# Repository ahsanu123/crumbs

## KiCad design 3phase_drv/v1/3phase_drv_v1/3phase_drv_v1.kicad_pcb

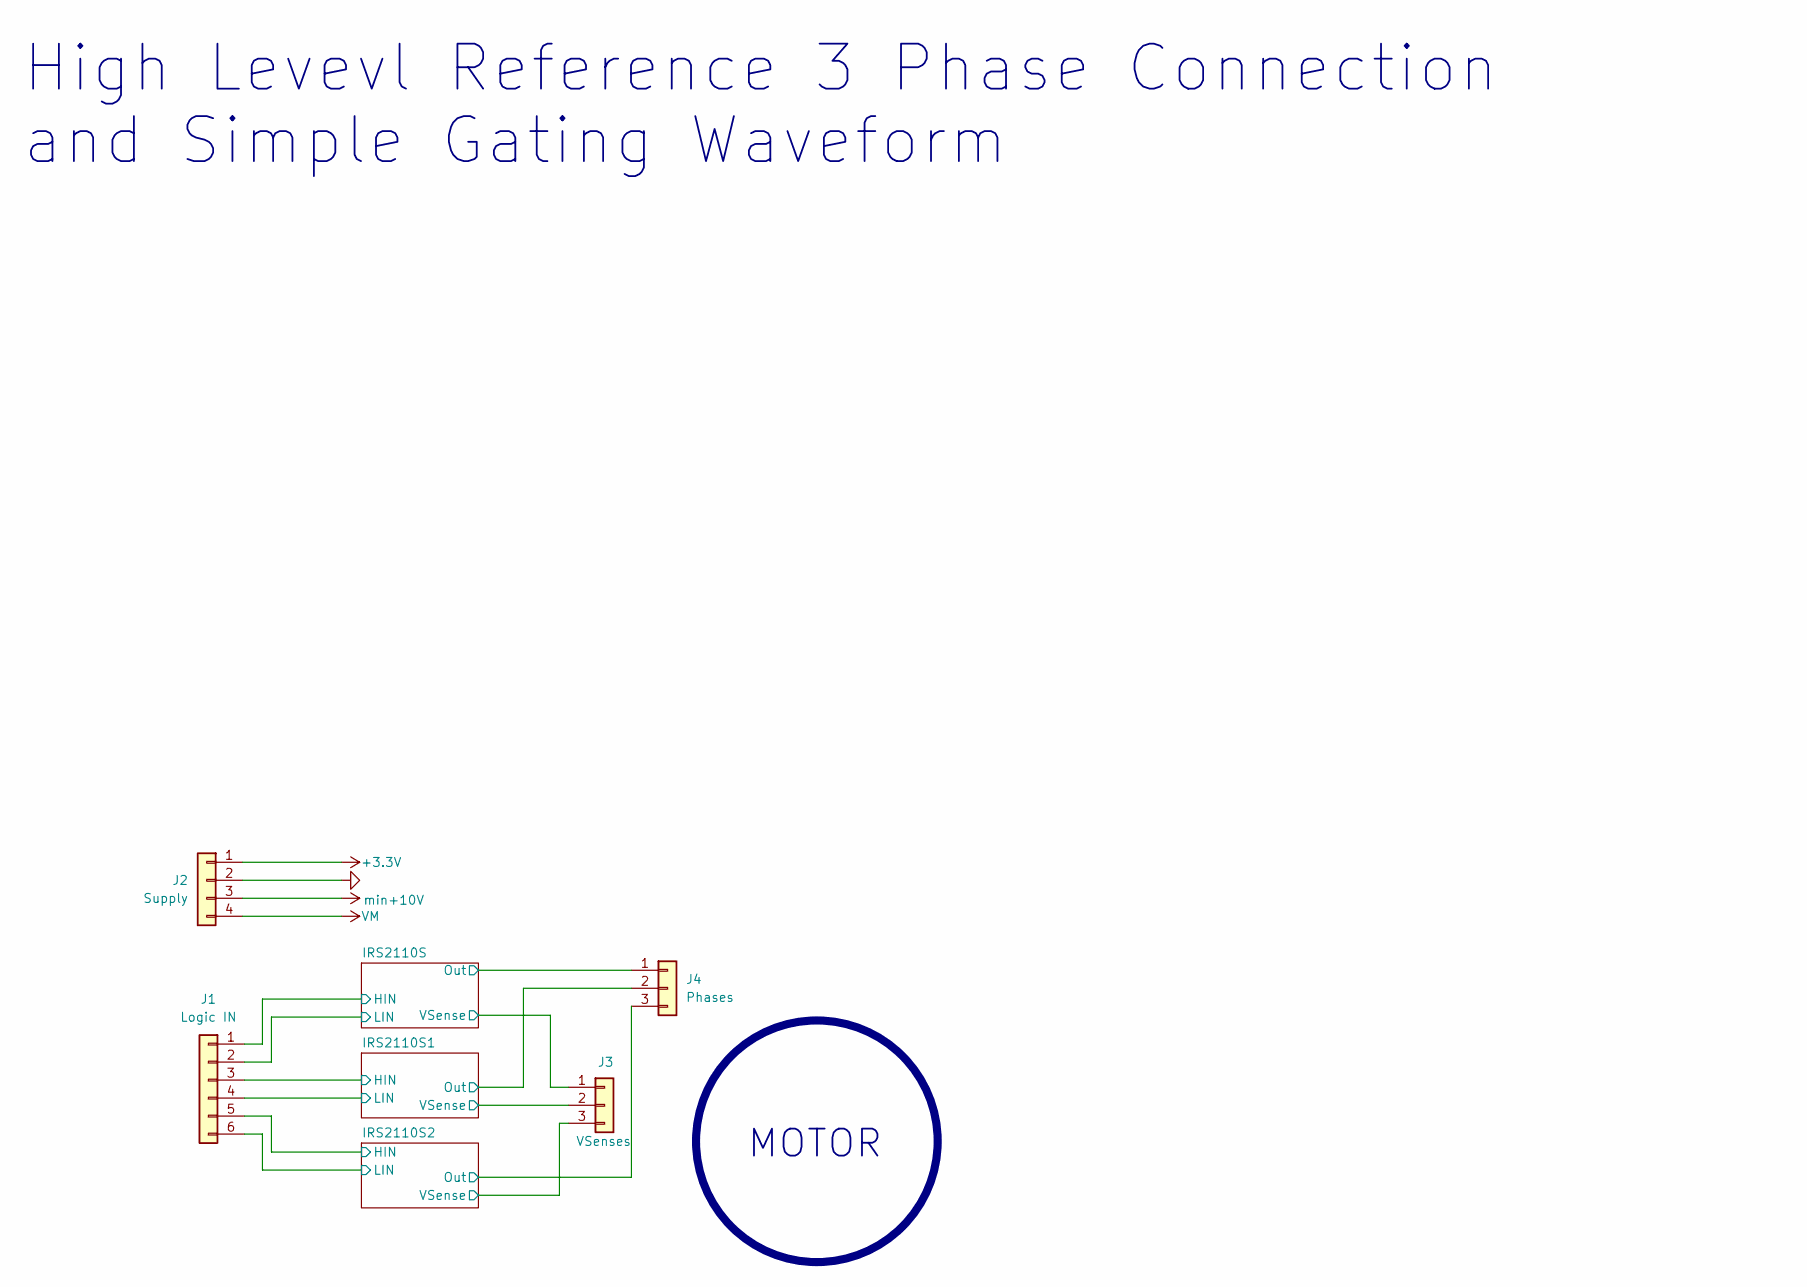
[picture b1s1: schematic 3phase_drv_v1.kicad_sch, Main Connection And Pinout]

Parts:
J1: Logic IN; PinHeader_1x06_P2.54mm_Vertical
J2: Supply; PinHeader_1x04_P2.54mm_Vertical
J3: VSenses; PinHeader_1x03_P2.54mm_Vertical
J4: Phases; PinHeader_1x03_P2.54mm_Vertical

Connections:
+3.3V: J2.1; also elsewhere on the board
/IRS2110S1/HIN: J1.3; also elsewhere on the board
/IRS2110S1/LIN: J1.4; also elsewhere on the board
/IRS2110S1/Out: J4.2; also elsewhere on the board
/IRS2110S1/VSense: J3.2; also elsewhere on the board
/IRS2110S2/HIN: J1.5; also elsewhere on the board
/IRS2110S2/LIN: J1.6; also elsewhere on the board
/IRS2110S2/Out: J4.3; also elsewhere on the board
/IRS2110S2/VSense: J3.3; also elsewhere on the board
/IRS2110S/HIN: J1.1; also elsewhere on the board
/IRS2110S/LIN: J1.2; also elsewhere on the board
/IRS2110S/Out: J4.1; also elsewhere on the board
/IRS2110S/VSense: J3.1; also elsewhere on the board
GND: J2.2; also elsewhere on the board
VM: J2.4; also elsewhere on the board
min+10V: J2.3; also elsewhere on the board

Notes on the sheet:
High Levevl Reference 3 Phase Connection and Simple Gating Waveform
MOTOR

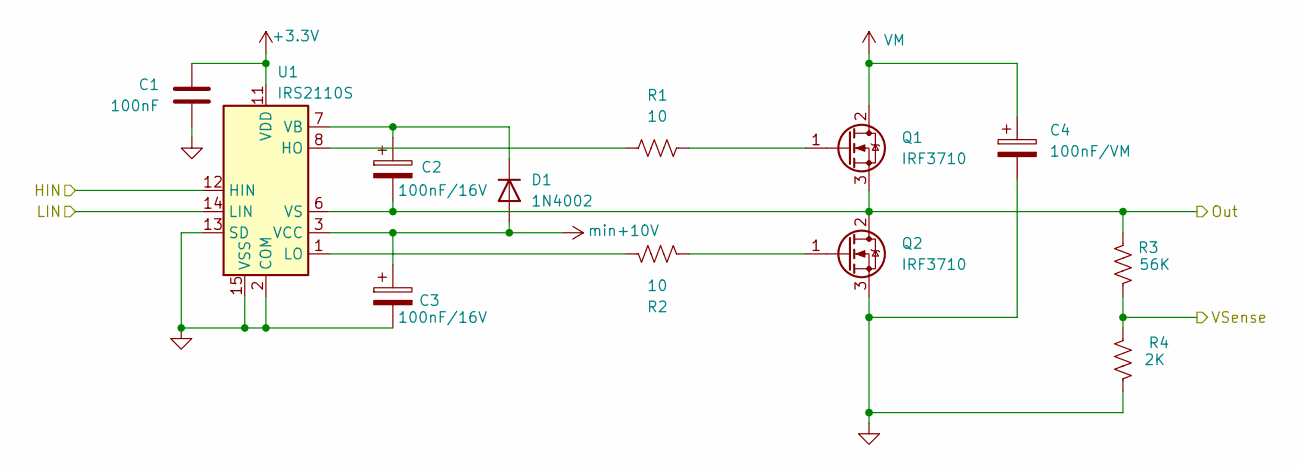
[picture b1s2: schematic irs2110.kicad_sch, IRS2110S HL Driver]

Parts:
C1: 100nF; C_0805_2012Metric
C2, C3: 100nF/16V; CP_Radial_D13.0mm_P5.00mm
C4: 100nF/VM; CP_Radial_D13.0mm_P5.00mm
D1: 1N4002; D_DO-41_SOD81_P10.16mm_Horizontal
Q1, Q2: IRF3710; TO-220-3_Horizontal_TabDown
R1, R2: 10; R_0805_2012Metric
R3: 56K; R_0805_2012Metric
R4: 2K; R_0805_2012Metric
U1: IRS2110S; SOIC-16W_7.5x10.3mm_P1.27mm

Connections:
+3.3V: C1.1, U1.11 (VDD); also elsewhere on the board
/IRS2110S1/HIN: U1.12 (HIN); also elsewhere on the board
/IRS2110S1/LIN: U1.14 (LIN); also elsewhere on the board
/IRS2110S1/Out: C2.2, Q1.3 (S), Q2.2 (D), R3.2, U1.6 (VS); also elsewhere on the board
/IRS2110S1/VSense: R3.1, R4.2; also elsewhere on the board
GND: C1.2, C3.2, C4.2, Q2.3 (S), R4.1, U1.2 (COM), U1.13 (SD), U1.15 (VSS); also elsewhere on the board
unnamed: C2.1, D1.1 (K), U1.7 (VB)
unnamed: Q1.1 (G), R1.2
unnamed: Q2.1 (G), R2.2
unnamed: R1.1, U1.8 (HO)
unnamed: R2.1, U1.1 (LO)
VM: C4.1, Q1.2 (D); also elsewhere on the board
min+10V: C3.1, D1.2 (A), U1.3 (VCC); also elsewhere on the board

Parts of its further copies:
C5, C9: 100nF; C_0805_2012Metric
C6, C7, C10, C11: 100nF/16V; CP_Radial_D13.0mm_P5.00mm
C8, C12: 100nF/VM; CP_Radial_D13.0mm_P5.00mm
D2, D3: 1N4002; D_DO-41_SOD81_P10.16mm_Horizontal
Q3, Q4, Q5, Q6: IRF3710; TO-220-3_Horizontal_TabDown
R5, R6, R9, R10: 10; R_0805_2012Metric
R7, R11: 56K; R_0805_2012Metric
R8, R12: 2K; R_0805_2012Metric
U2, U3: IRS2110S; SOIC-16W_7.5x10.3mm_P1.27mm

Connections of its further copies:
+3.3V: C5.1, C9.1, U2.11 (VDD), U3.11 (VDD); also elsewhere on the board
/IRS2110S2/HIN: U2.12 (HIN); also elsewhere on the board
/IRS2110S2/LIN: U2.14 (LIN); also elsewhere on the board
/IRS2110S2/Out: C6.2, Q3.3 (S), Q4.2 (D), R7.2, U2.6 (VS); also elsewhere on the board
/IRS2110S2/VSense: R7.1, R8.2; also elsewhere on the board
/IRS2110S/HIN: U3.12 (HIN); also elsewhere on the board
/IRS2110S/LIN: U3.14 (LIN); also elsewhere on the board
/IRS2110S/Out: C10.2, Q5.3 (S), Q6.2 (D), R11.2, U3.6 (VS); also elsewhere on the board
/IRS2110S/VSense: R11.1, R12.2; also elsewhere on the board
GND: C5.2, C7.2, C8.2, C9.2, C11.2, C12.2, Q4.3 (S), Q6.3 (S), R8.1, R12.1, U2.2 (COM), U2.13 (SD), U2.15 (VSS), U3.2 (COM), U3.13 (SD), U3.15 (VSS); also elsewhere on the board
unnamed: C6.1, D2.1 (K), U2.7 (VB)
unnamed: C10.1, D3.1 (K), U3.7 (VB)
unnamed: Q3.1 (G), R5.2
unnamed: Q4.1 (G), R6.2
unnamed: Q5.1 (G), R9.2
unnamed: Q6.1 (G), R10.2
unnamed: R5.1, U2.8 (HO)
unnamed: R6.1, U2.1 (LO)
unnamed: R9.1, U3.8 (HO)
unnamed: R10.1, U3.1 (LO)
VM: C8.1, C12.1, Q3.2 (D), Q5.2 (D); also elsewhere on the board
min+10V: C7.1, C11.1, D2.2 (A), D3.2 (A), U2.3 (VCC), U3.3 (VCC); also elsewhere on the board

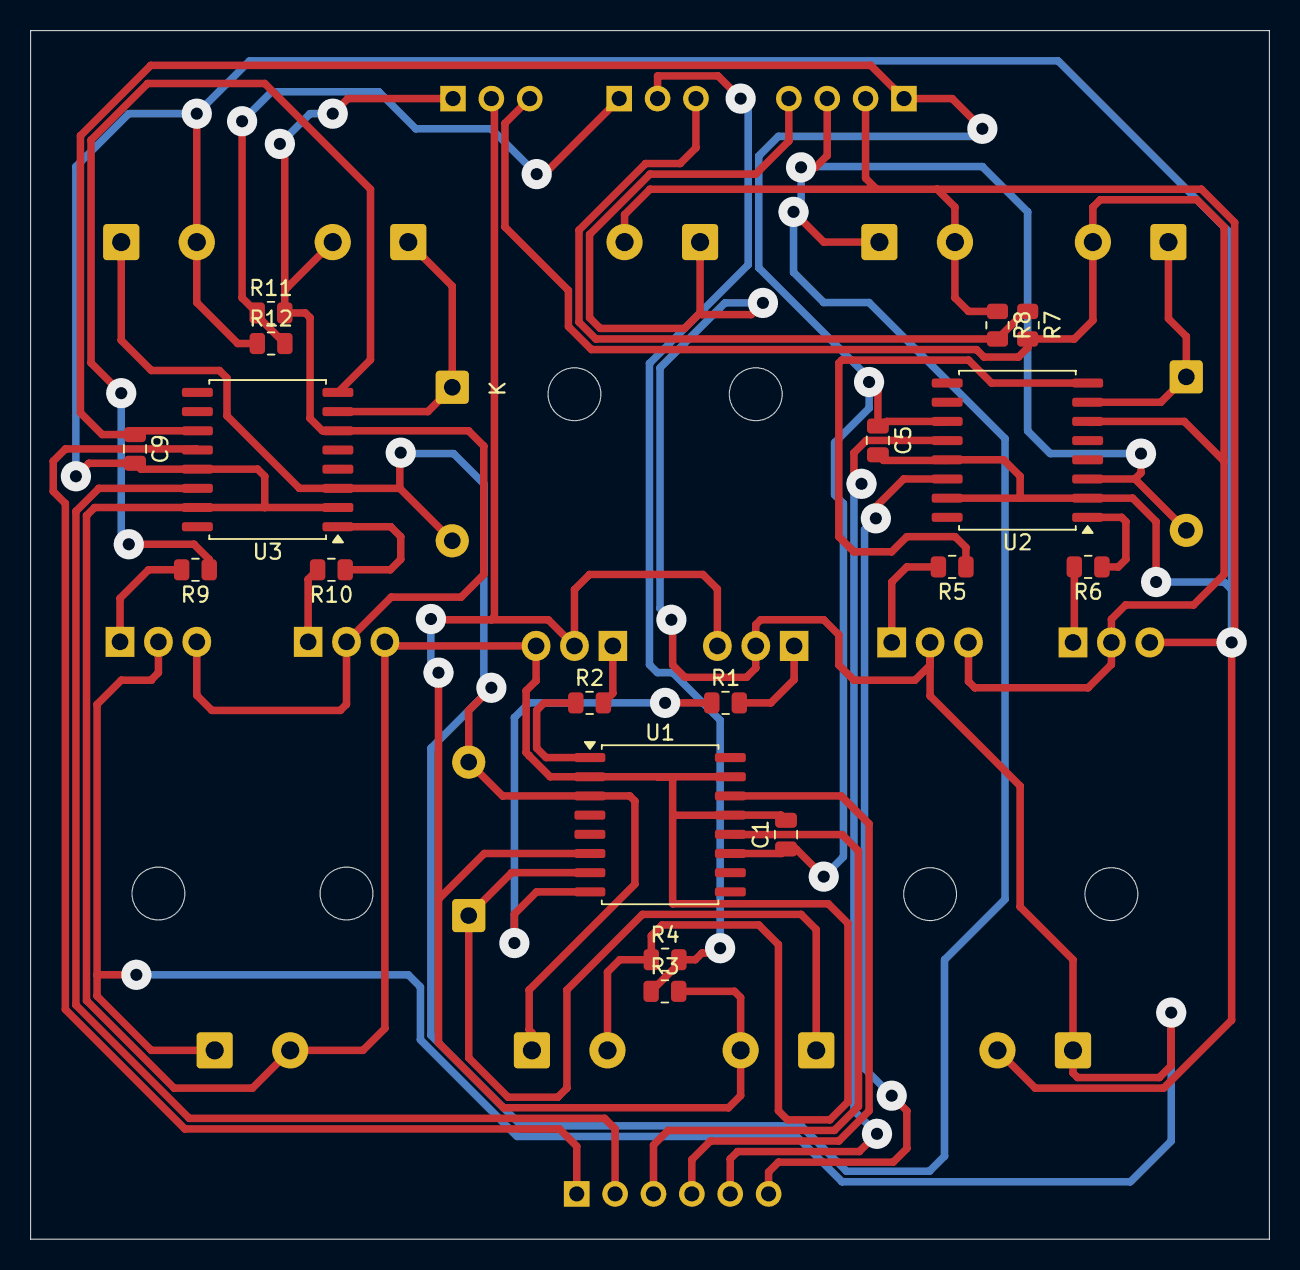
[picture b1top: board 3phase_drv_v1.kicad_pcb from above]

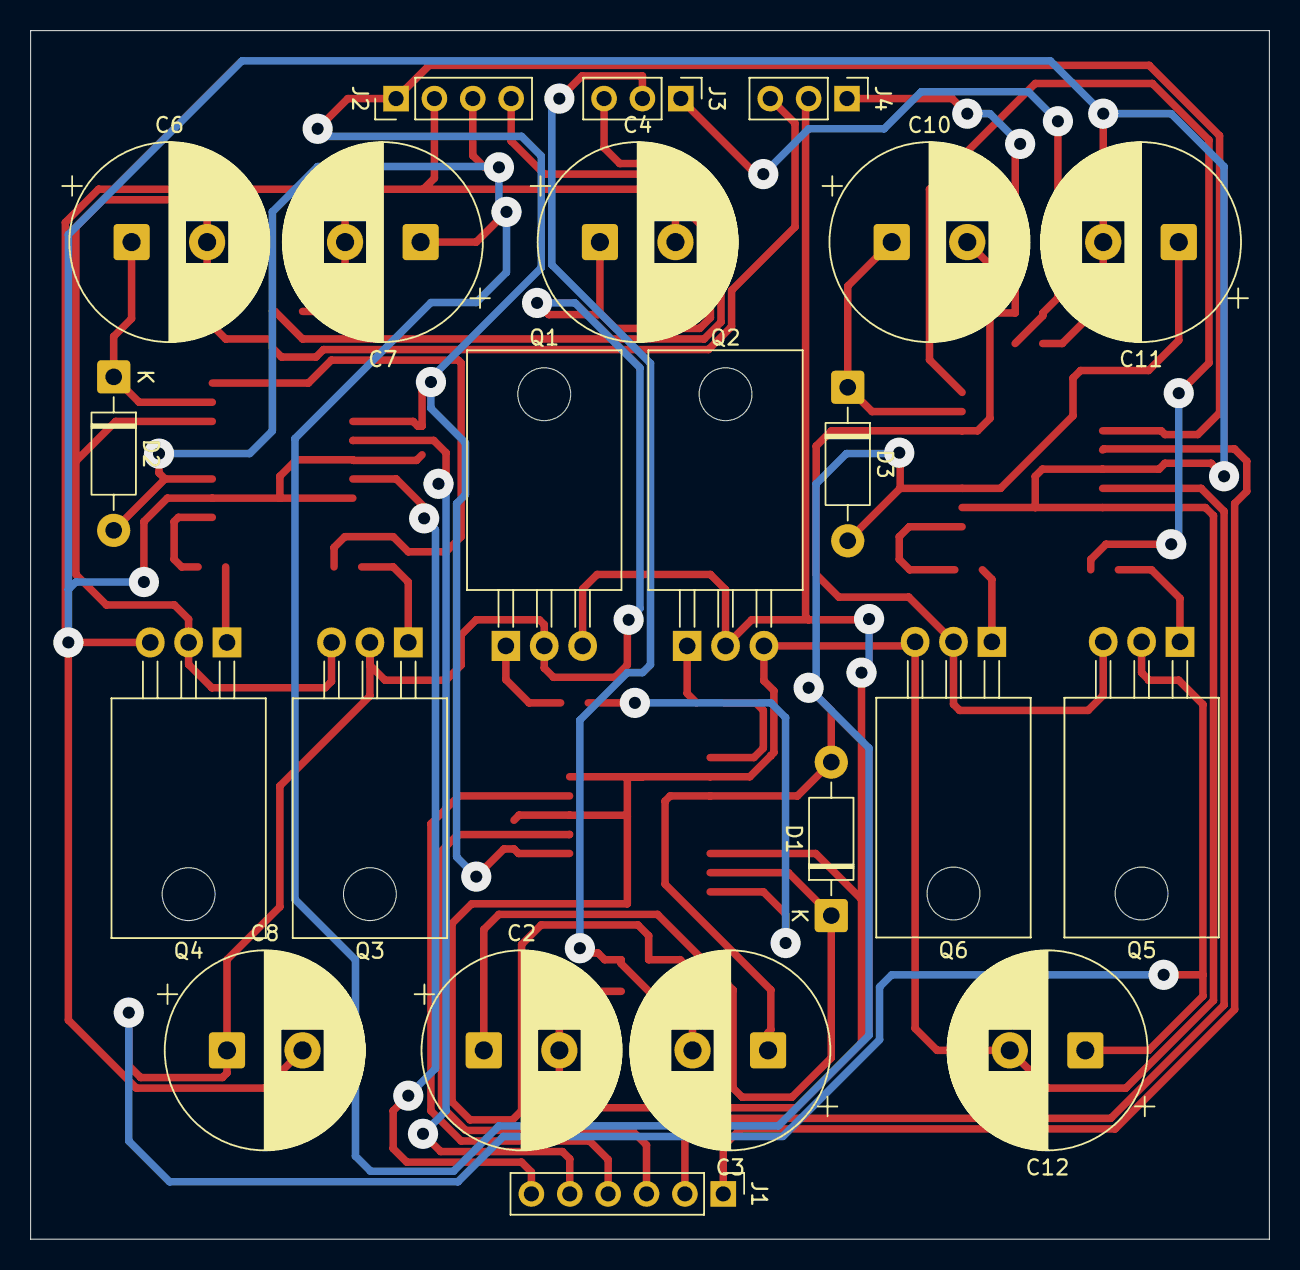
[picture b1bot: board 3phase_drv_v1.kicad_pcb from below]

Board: 2 copper layers, 82.0 x 80.0 mm, 40 parts (22 on the bottom side), 31 nets.

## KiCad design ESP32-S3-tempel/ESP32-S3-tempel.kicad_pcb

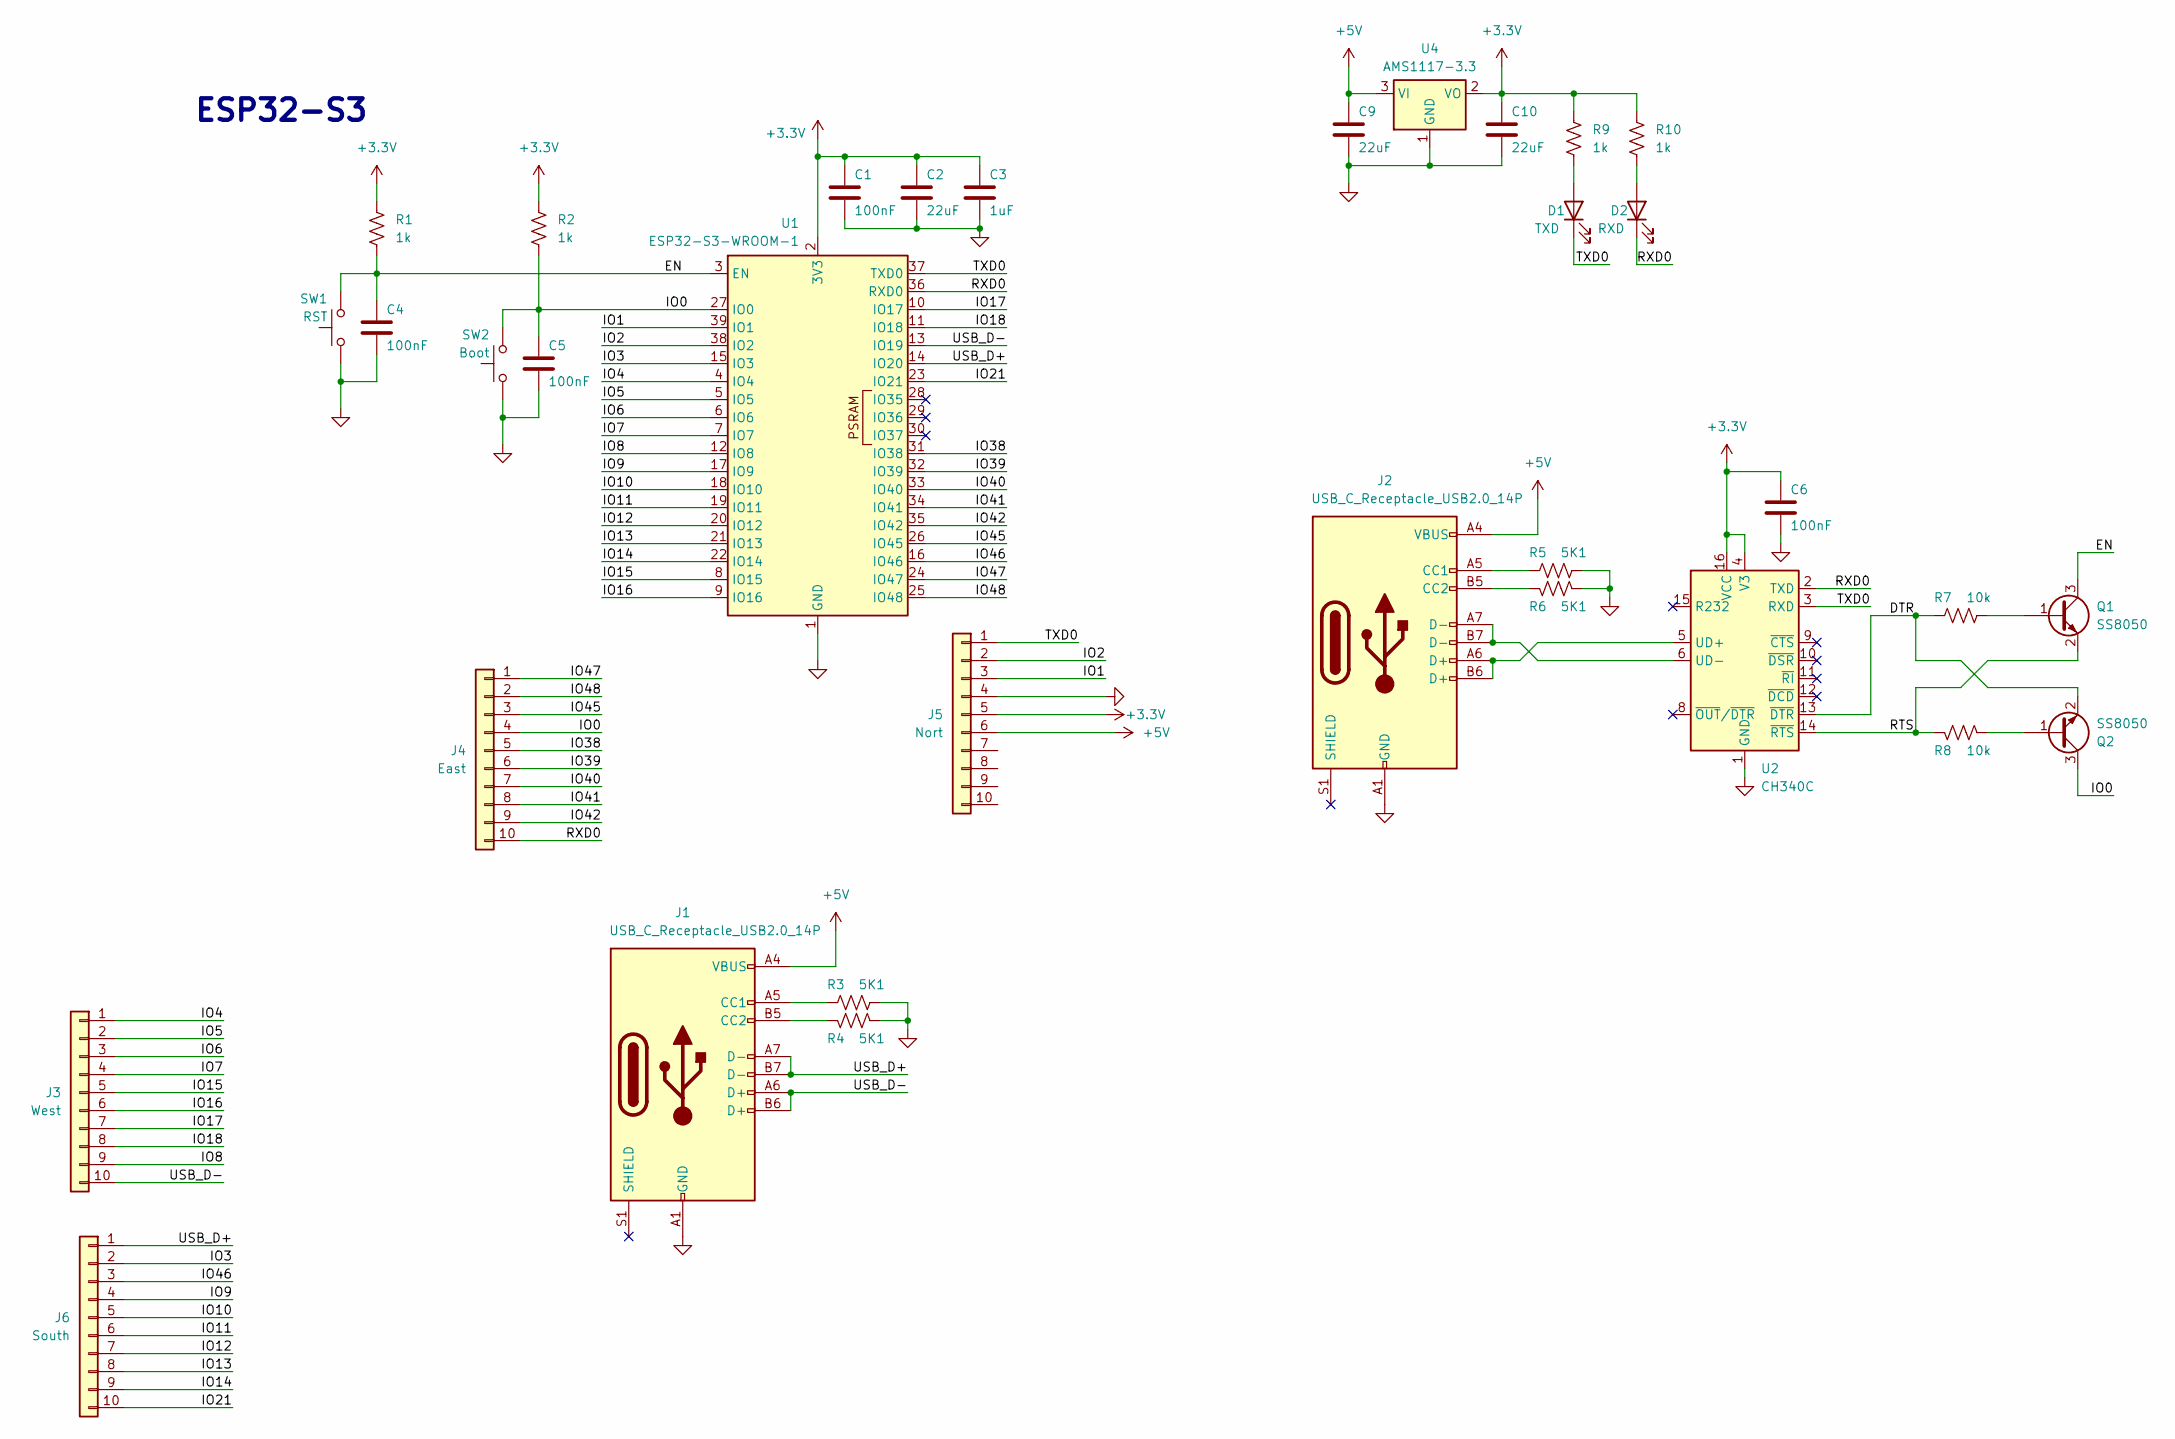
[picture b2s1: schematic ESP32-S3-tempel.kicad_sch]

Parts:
C1, C4, C5, C6: 100nF; C_0805_2012Metric_Pad1.18x1.45mm_HandSolder
C2, C9, C10: 22uF; C_0805_2012Metric_Pad1.18x1.45mm_HandSolder
C3: 1uF; C_0805_2012Metric_Pad1.18x1.45mm_HandSolder
D1: TXD; LED_1206_3216Metric_Pad1.42x1.75mm_HandSolder
D2: RXD; LED_1206_3216Metric_Pad1.42x1.75mm_HandSolder
J1, J2: USB_C_Receptacle_USB2.0_14P; USB_C_Receptacle_GCT_USB4110
J3: West; PinHeader_1x10_P2.54mm_Vertical
J4: East; PinHeader_1x10_P2.54mm_Vertical
J5: Nort; PinHeader_1x10_P2.54mm_Vertical
J6: South; PinHeader_1x10_P2.54mm_Vertical
Q1, Q2: SS8050; SOT-23_Handsoldering
R1, R2, R9, R10: 1k; R_0805_2012Metric_Pad1.20x1.40mm_HandSolder
R3, R4, R5, R6: 5K1; R_0805_2012Metric_Pad1.20x1.40mm_HandSolder
R7, R8: 10k; R_0805_2012Metric_Pad1.20x1.40mm_HandSolder
SW1: RST; SW_Push_1P1T_NO_6x6mm_H9.5mm
SW2: Boot; SW_Push_1P1T_NO_6x6mm_H9.5mm
U1: ESP32-S3-WROOM-1; ESP32-S3-WROOM-1U
U2: CH340C; SOIC-16_3.9x9.9mm_P1.27mm
U4: AMS1117-3.3; SOT-223-3_TabPin2

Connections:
+3.3V: C1.1, C2.1, C3.1, C6.1, C10.1, J5.5, R1.1, R2.1, R9.1, R10.1, U1.2 (3V3), U2.4 (V3), U2.16 (VCC), U4.2 (VO)
+5V: C9.1, J1.A4 (VBUS), J1.A9 (VBUS), J1.B4 (VBUS), J1.B9 (VBUS), J2.A4 (VBUS), J2.A9 (VBUS), J2.B4 (VBUS), J2.B9 (VBUS), J5.6, U4.3 (VI)
/DTR: Q2.2 (E), R7.2, U2.13 (~DTR)
/EN: C4.1, Q1.3 (C), R1.2, SW1.2, U1.3 (EN)
/IO0: C5.1, J4.4, Q2.3 (C), R2.2, SW2.2, U1.27 (IO0)
/IO1: J5.3, U1.39 (IO1)
/IO2: J5.2, U1.38 (IO2)
/IO3: J6.2, U1.15 (IO3)
/IO4: J3.1, U1.4 (IO4)
/IO5: J3.2, U1.5 (IO5)
/IO6: J3.3, U1.6 (IO6)
/IO7: J3.4, U1.7 (IO7)
/IO8: J3.9, U1.12 (IO8)
/IO9: J6.4, U1.17 (IO9)
/IO10: J6.5, U1.18 (IO10)
/IO11: J6.6, U1.19 (IO11)
/IO12: J6.7, U1.20 (IO12)
/IO13: J6.8, U1.21 (IO13)
/IO14: J6.9, U1.22 (IO14)
/IO15: J3.5, U1.8 (IO15)
/IO16: J3.6, U1.9 (IO16)
/IO17: J3.7, U1.10 (IO17)
/IO18: J3.8, U1.11 (IO18)
/IO21: J6.10, U1.23 (IO21)
/IO38: J4.5, U1.31 (IO38)
/IO39: J4.6, U1.32 (IO39)
/IO40: J4.7, U1.33 (IO40)
/IO41: J4.8, U1.34 (IO41)
/IO42: J4.9, U1.35 (IO42)
/IO45: J4.3, U1.26 (IO45)
/IO46: J6.3, U1.16 (IO46)
/IO47: J4.1, U1.24 (IO47)
/IO48: J4.2, U1.25 (IO48)
/RTS: Q1.2 (E), R8.2, U2.14 (~RTS)
/RXD0: D2.1 (K), J4.10, U1.36 (RXD0), U2.2 (TXD)
/TXD0: D1.1 (K), J5.1, U1.37 (TXD0), U2.3 (RXD)
/USB_D+: J1.A7 (D-), J1.B7 (D-), J6.1, U1.14 (IO20)
/USB_D-: J1.A6 (D+), J1.B6 (D+), J3.10, U1.13 (IO19)
GND: C1.2, C2.2, C3.2, C4.2, C5.2, C6.2, C9.2, C10.2, J1.A1 (GND), J1.A12 (GND), J1.B1 (GND), J1.B12 (GND), J2.A1 (GND), J2.A12 (GND), J2.B1 (GND), J2.B12 (GND), J5.4, R3.1, R4.1, R5.1, R6.1, SW1.1, SW2.1, U1.1 (GND), U1.40 (GND), U1.41 (GND), U2.1 (GND), U4.1 (GND)
unnamed: D1.2 (A), R9.2
unnamed: D2.2 (A), R10.2
unnamed: J1.A5 (CC1), R3.2
unnamed: J1.B5 (CC2), R4.2
unnamed: J2.A5 (CC1), R5.2
unnamed: J2.B5 (CC2), R6.2
unnamed: Q1.1 (B), R7.1
unnamed: Q2.1 (B), R8.1
unnamed: J2.A6 (D+), J2.B6 (D+), U2.5 (UD+)
unnamed: J2.A7 (D-), J2.B7 (D-), U2.6 (UD-)

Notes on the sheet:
ESP32-S3

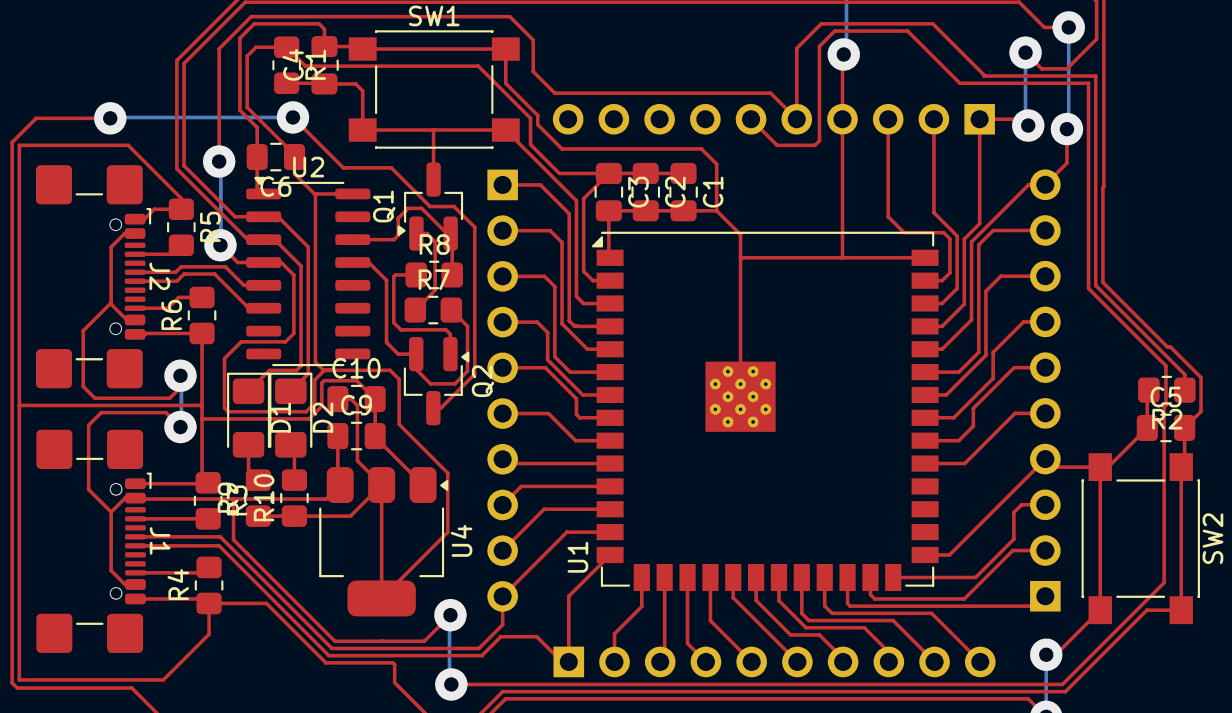
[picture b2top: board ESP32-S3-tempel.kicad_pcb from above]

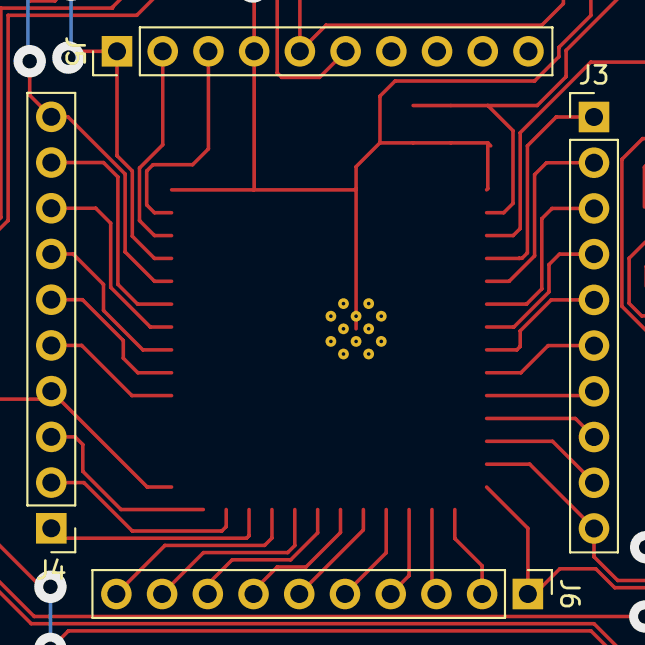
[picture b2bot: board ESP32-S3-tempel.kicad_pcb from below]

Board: 2 copper layers, 33 parts (4 on the bottom side), 49 nets.

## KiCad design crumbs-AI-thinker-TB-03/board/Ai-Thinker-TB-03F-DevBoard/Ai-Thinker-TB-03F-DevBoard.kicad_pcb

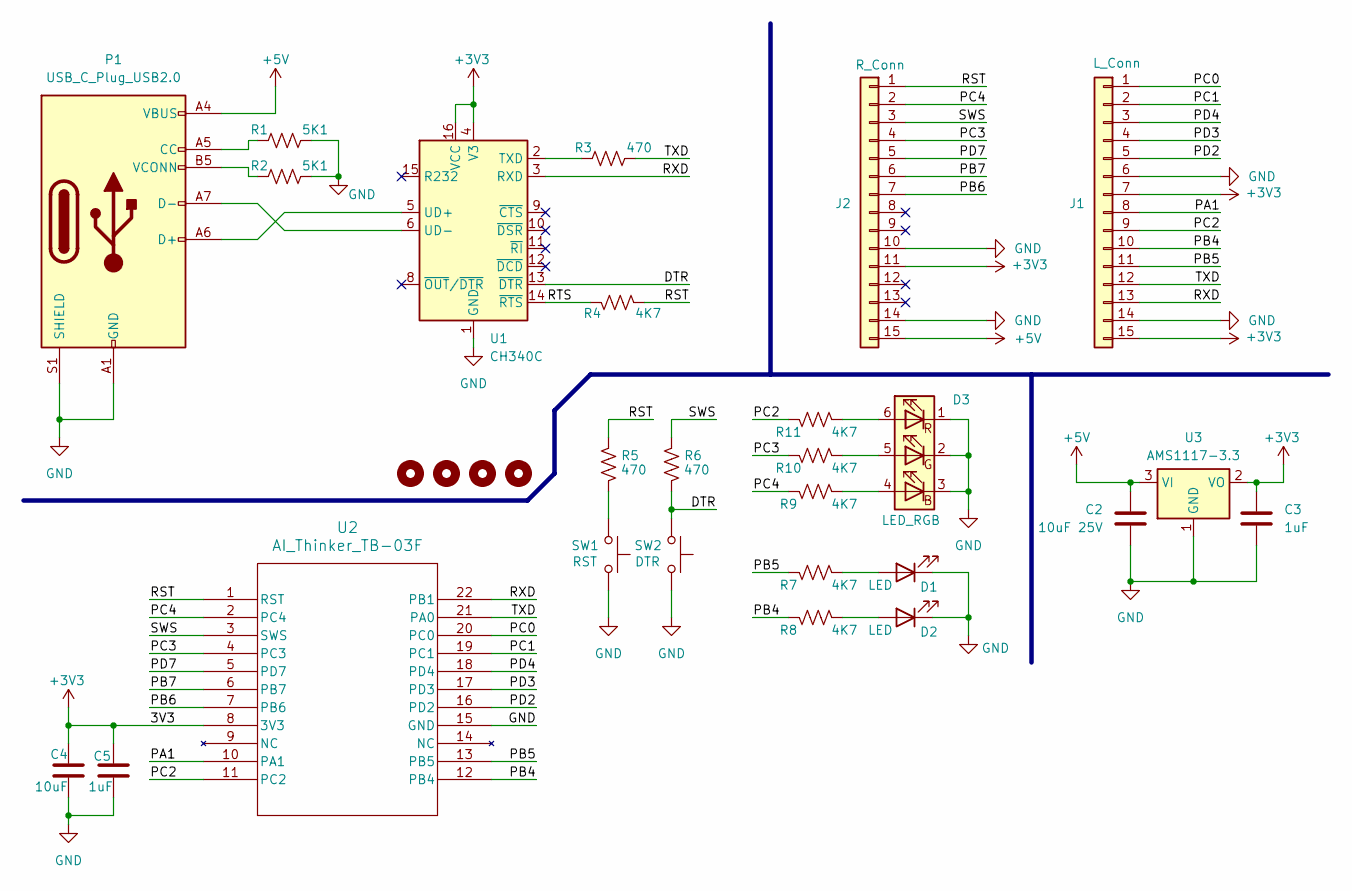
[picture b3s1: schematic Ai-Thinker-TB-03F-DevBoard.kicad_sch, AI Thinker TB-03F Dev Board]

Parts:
C2: 10uF 25V; C_0603_1608Metric
C3, C5: 1uF; C_0603_1608Metric
C4: 10uF; C_0603_1608Metric
D1, D2: LED; LED_0603_1608Metric
D3: LED_RGB; LED_WS2812_PLCC6_5.0x5.0mm_P1.6mm
H1, H2, H3, H4: MountingHole; MountingHole_3mm
J1: L_Conn; PinHeader_1x15_P2.54mm_Vertical
J2: R_Conn; PinHeader_1x15_P2.54mm_Vertical
P1: USB_C_Plug_USB2.0; USB_C_Receptacle_XKB_U262-16XN-4BVC11
R1, R2: 5K1; R_0603_1608Metric
R3, R5, R6: 470; R_0603_1608Metric
R4, R7, R8, R9, R10, R11: 4K7; R_0603_1608Metric
SW1: RST; SW_Push_SPST_NO_Alps_SKRK
SW2: DTR; SW_Push_SPST_NO_Alps_SKRK
U1: CH340C; SOIC-16_3.9x9.9mm_P1.27mm
U2: AI_Thinker_TB-03F; TB-03F_AIT
U3: AMS1117-3.3; SOT-223-3_TabPin2

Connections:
+3V3: C3.1, C4.1, C5.1, J1.7, J1.15, J2.11, U1.4 (V3), U1.16 (VCC), U2.8 (3V3), U3.2 (VO)
+5V: C2.1, J2.15, P1.A4 (VBUS), P1.A9 (VBUS), P1.B4 (VBUS), P1.B9 (VBUS), U3.3 (VI)
/DTR: R6.2, SW2.2, U1.13 (~DTR)
/PA1: J1.8, U2.10 (PA1)
/PB4: J1.10, R8.2, U2.12 (PB4)
/PB5: J1.11, R7.2, U2.13 (PB5)
/PB6: J2.7, U2.7 (PB6)
/PB7: J2.6, U2.6 (PB7)
/PC0: J1.1, U2.20 (PC0)
/PC1: J1.2, U2.19 (PC1)
/PC2: J1.9, R11.2, U2.11 (PC2)
/PC3: J2.4, R10.2, U2.4 (PC3)
/PC4: J2.2, R9.2, U2.2 (PC4)
/PD2: J1.5, U2.16 (PD2)
/PD3: J1.4, U2.17 (PD3)
/PD4: J1.3, U2.18 (PD4)
/PD7: J2.5, U2.5 (PD7)
/RST: J2.1, R4.1, R5.1, U2.1 (RST)
/RTS: R4.2, U1.14 (~RTS)
/RXD: J1.13, U1.3 (RXD), U2.22 (PB1)
/SWS: J2.3, R6.1, U2.3 (SWS)
/TXD: J1.12, R3.1, U2.21 (PA0)
GND: C2.2, C3.2, C4.2, C5.2, D1.1 (K), D2.1 (K), D3.1 (RK), D3.2 (GK), D3.3 (BK), J1.6, J1.14, J2.10, J2.14, P1.A1 (GND), P1.A12 (GND), P1.B1 (GND), P1.B12 (GND), P1.S1 (SHIELD), R1.1, R2.1, SW1.1, SW2.1, U1.1 (GND), U2.15 (GND), U3.1 (GND)
unnamed: D1.2 (A), R7.1
unnamed: D2.2 (A), R8.1
unnamed: D3.4 (BA), R9.1
unnamed: D3.5 (GA), R10.1
unnamed: D3.6 (RA), R11.1
unnamed: P1.A5 (CC), R1.2
unnamed: P1.A6 (D+), U1.5 (UD+)
unnamed: P1.A7 (D-), U1.6 (UD-)
unnamed: P1.B5 (VCONN), R2.2
unnamed: R5.2, SW1.2
unnamed: R3.2, U1.2 (TXD)

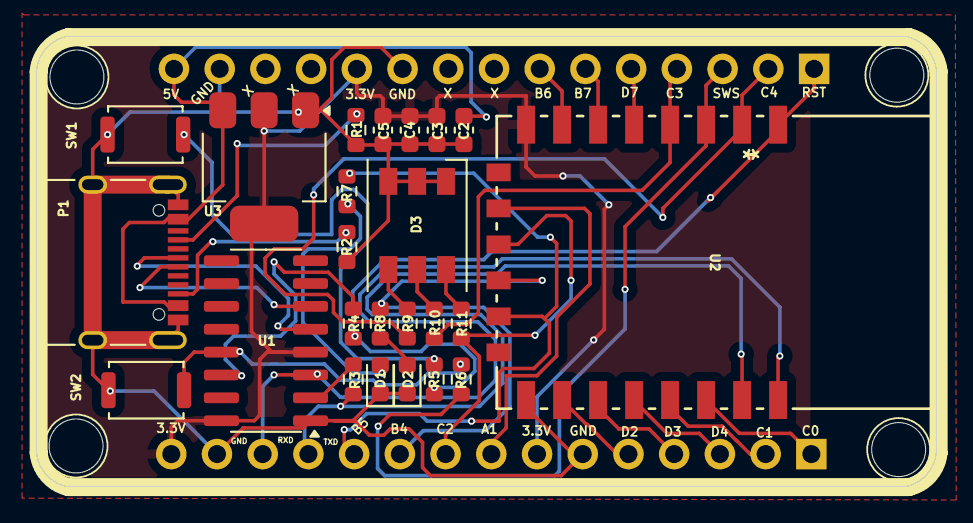
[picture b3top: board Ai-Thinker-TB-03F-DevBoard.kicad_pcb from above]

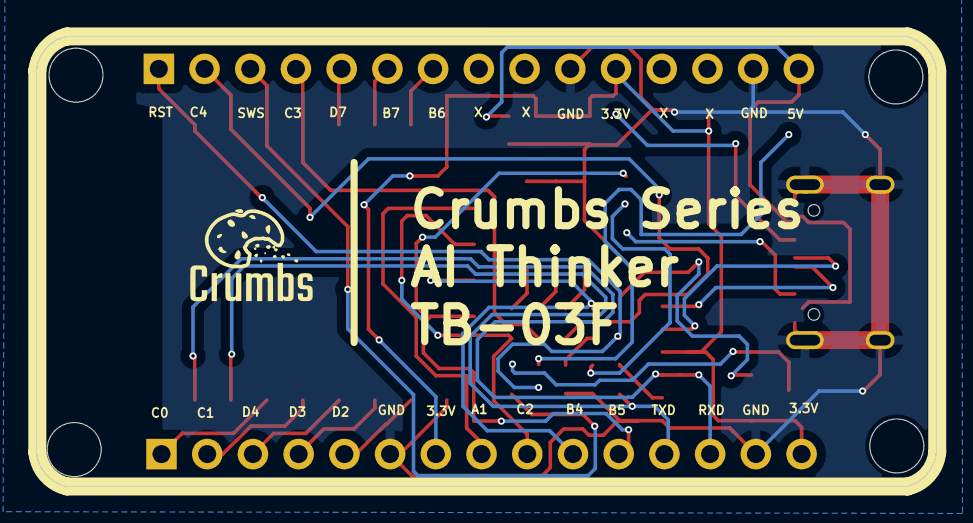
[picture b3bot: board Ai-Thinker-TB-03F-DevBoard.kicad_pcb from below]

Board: 2 copper layers, 50.0 x 25.0 mm, 31 parts (2 on the bottom side), 34 nets.

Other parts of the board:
G12: LOGO; Crumbs-Logo_Footprint_13x13
